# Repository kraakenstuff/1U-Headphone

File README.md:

# 1U-Headphone
1U Eurorack headphone output module based on Befaco Output v3 (https://www.befaco.org/docs/Output/Output_V3_schematic.pdf)

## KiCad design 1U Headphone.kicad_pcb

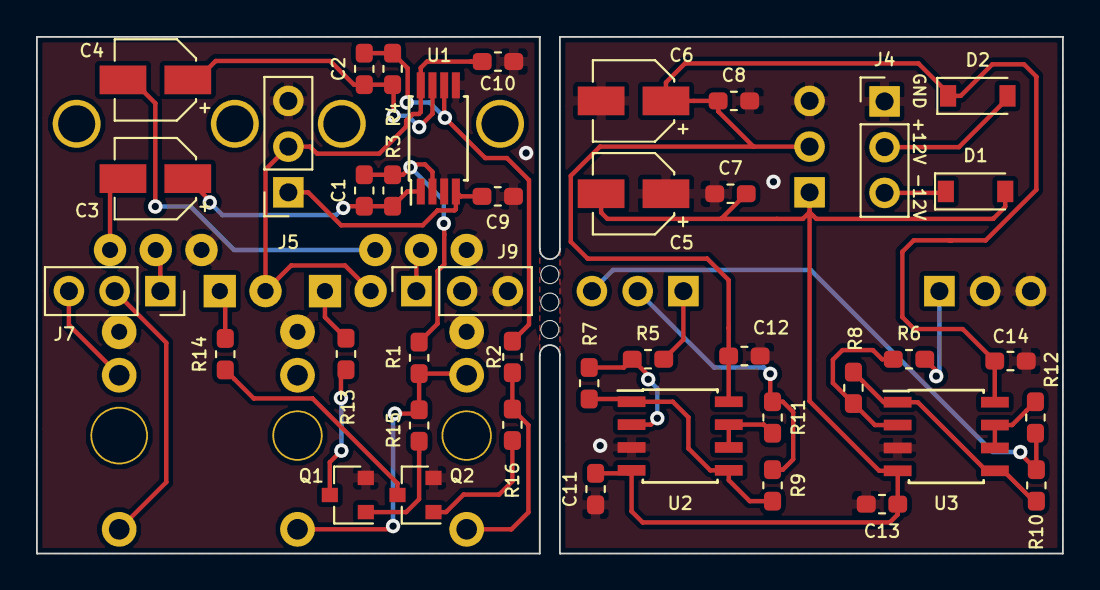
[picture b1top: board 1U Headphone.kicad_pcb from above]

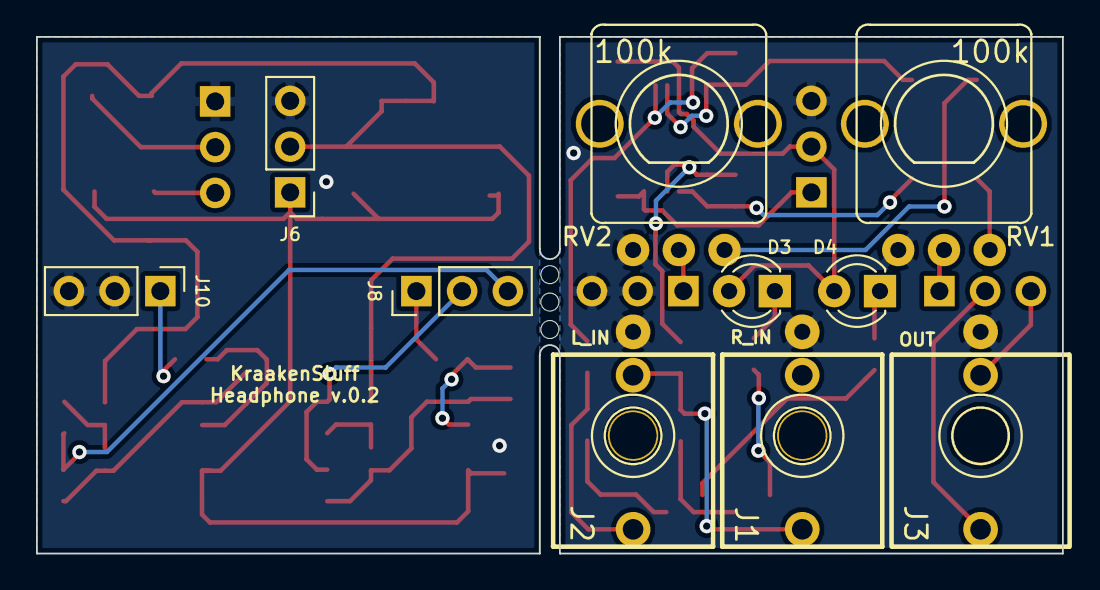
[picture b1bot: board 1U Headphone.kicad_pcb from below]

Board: 2 copper layers, 57.0 x 28.7 mm, 51 parts (10 on the bottom side), 33 nets.

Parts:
C1, C2: 10p; C_0603_1608Metric_Pad1.05x0.95mm_HandSolder
C3, C4, C5, C6: 10uF; CP_Elec_4x5.7
C7, C8, C9, C10, C11, C12, C13, C14: 100n; C_0603_1608Metric_Pad1.05x0.95mm_HandSolder
D1, D2: 1N5817; D_SOD-123
D3, D4: LED; LED_D3.0mm
J1: R_IN; PJ301M-12
J2: L_IN; PJ301M-12
J3: OUT; PJ366ST
J4: PWR; PinHeader_1x03_P2.54mm_Vertical
J5: PWR_C; PinSocket_1x03_P2.54mm_Vertical
J6: PWR_M; PinHeader_1x03_P2.54mm_Vertical
J7: POT_R_C; PinSocket_1x03_P2.54mm_Vertical
J8: POT_R_M; PinHeader_1x03_P2.54mm_Vertical
J9: POT_L_C; PinSocket_1x03_P2.54mm_Vertical
J10: POT_L_M; PinHeader_1x03_P2.54mm_Vertical
Q1, Q2: MMBT3904; SOT-23
R1, R2, R15, R16: 100k; R_0603_1608Metric_Pad1.05x0.95mm_HandSolder
R3, R4: 39k; R_0603_1608Metric_Pad1.05x0.95mm_HandSolder
R5, R6, R7, R8: 10k; R_0603_1608Metric_Pad1.05x0.95mm_HandSolder
R9, R10, R11, R12: 75; R_0603_1608Metric_Pad1.05x0.95mm_HandSolder
R13, R14: 1k; R_0603_1608Metric_Pad1.05x0.95mm_HandSolder
RV1, RV2: 100k; POT-9MM-ALPHA
U1: TL072; TSSOP-8_4.4x3mm_P0.65mm
U2, U3: NE5532; SOIC-8_3.9x4.9mm_P1.27mm

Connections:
+12V: C6.1, C8.1, C10.1, C12.1, C14.1, D2.1, D3.2, D4.2, J5.2, J6.2, U1.8, U2.8, U3.8
-12V: C5.2, C7.2, C9.2, C11.2, C13.2, D1.2, J5.1, J6.1, U1.4, U2.4, U3.4
GND: C5.1, C6.2, C7.1, C8.2, C9.1, C10.2, C11.1, C12.2, C13.1, C14.2, J1.S, J2.S, J3.S, J4.1, J5.3, J6.3, J9.2, J9.3, J10.2, J10.3, Q1.2, Q2.2, RV1.1, RV2.1, U1.3, U1.5, U2.3, U3.3
unnamed: C1.1, C3.1, R3.1, U1.1
unnamed: C1.2, R1.1, R3.2, U1.2
unnamed: C2.1, C4.1, R4.1, U1.7
unnamed: C2.2, R2.1, R4.2, U1.6
unnamed: C3.2, RV1.3
unnamed: C4.2, RV2.3
unnamed: D1.1, J4.3
unnamed: D2.2, J4.2
unnamed: D3.1, R13.2
unnamed: D4.1, R14.2
unnamed: J1.T, J2.TN, R1.2, R15.1
unnamed: J2.T, R2.2, R16.1
unnamed: Q1.1, R15.2
unnamed: Q1.3, R13.1
unnamed: Q2.1, R16.2
unnamed: Q2.3, R14.1
unnamed: R5.1, R7.2, U2.2
unnamed: R6.1, R8.2, U3.2
unnamed: R7.1, R9.2, U2.1, U2.5
unnamed: R8.1, R10.2, U3.1, U3.5
unnamed: R11.2, U2.6, U2.7
unnamed: R12.2, U3.6, U3.7
OUT_L_C: J3.R, J7.3
OUT_L_M: J8.3, R10.1, R12.1
OUT_R_C: J3.T, J7.2
OUT_R_M: J8.2, R9.1, R11.1
POT_L_C: J9.1, RV2.2
POT_L_M: J10.1, R6.2
POT_R_C: J7.1, RV1.2
POT_R_M: J8.1, R5.2

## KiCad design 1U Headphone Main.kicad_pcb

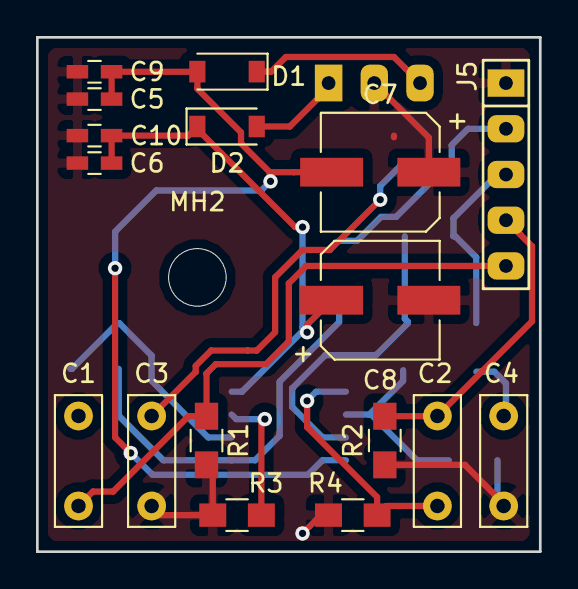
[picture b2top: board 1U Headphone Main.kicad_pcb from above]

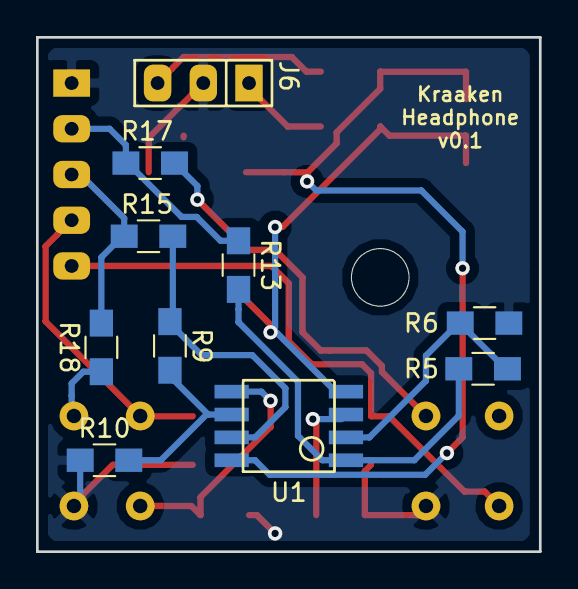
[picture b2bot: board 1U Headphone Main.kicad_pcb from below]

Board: 2 copper layers, 27.9 x 28.6 mm, 28 parts (10 on the bottom side), 17 nets.

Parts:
C1, C2, C3, C4: C; C_Rect_L7.2mm_W2.5mm_P5.00mm_FKS2_FKP2_MKS2_MKP2
C5, C6, C9, C10: C; C_0603_HandSoldering
C7, C8: CP; CP_Elec_6.3x7.7
D1, D2: 1N5817; D_SOD-123
J5: Header_1x05; Header 1x5
J6: Header_1x03; Header 1x3
MH2: MountingHole; MountingHole_3.2mm_M3
R1, R2, R3, R4, R5, R6, R9, R10, R13, R15, R17, R18: R; R_0805_HandSoldering
U1: NJM2068; DMP8

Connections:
+12V: C6.1, C8.1, C10.1, D2.1, U1.4
-12V: C5.2, C7.2, C9.2, D1.2, U1.8
GND: C3.1, C4.1, C5.1, C6.2, C7.1, C8.2, C9.1, C10.2, J5.1, J6.2, R1.2, R2.2, R3.2, R4.2, R6.1, R10.1
L_IN: C1.2, J5.5, R1.1
L_OUT: J5.2, R13.1, R17.2
unnamed: C1.1, R3.1, U1.3
unnamed: C2.1, R4.1, U1.5
unnamed: C3.2, R17.1
unnamed: C4.2, R18.1
unnamed: D1.1, J6.3
unnamed: D2.2, J6.1
unnamed: R5.2, R6.2, U1.2
unnamed: R9.2, R10.2, U1.6
unnamed: R5.1, R13.2, U1.1
unnamed: R9.1, R15.2, U1.7
R_IN: C2.2, J5.4, R2.1
R_OUT: J5.3, R15.1, R18.2

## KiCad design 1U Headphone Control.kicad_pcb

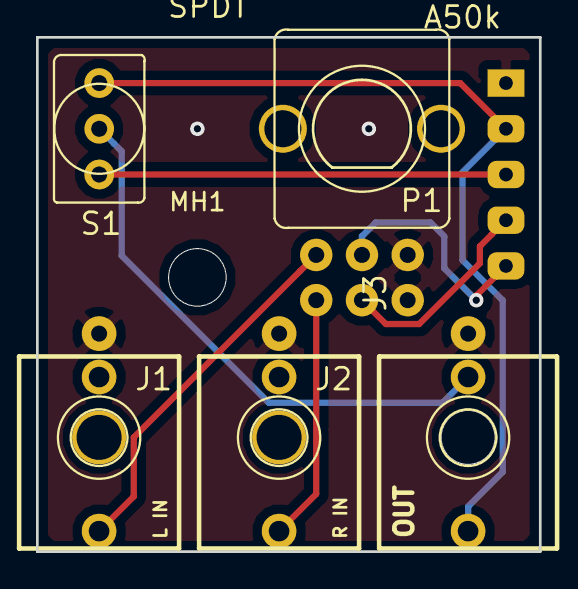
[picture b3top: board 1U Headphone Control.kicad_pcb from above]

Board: 2 copper layers, 27.9 x 28.6 mm, 7 parts (1 on the bottom side), 8 nets.

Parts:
J1: L IN; PJ301M-12
J2: R IN; PJ301M-12
J3: OUT; PJ366ST
J4: Header_1x05; Header 1x5
MH1: MountingHole; MountingHole_3.2mm_M3
P1: A50k; POT-9MM-ALPHA-DUAL
S1: SPDT; SPDT-SUB

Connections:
GND: J1.1, J2.1, J3.1, J4.1, P1.3, P1.6
L_IN: J4.5, P1.2
L_OUT: J3.3, J4.2, S1.3
unnamed: J1.3, P1.1
unnamed: J2.3, P1.4
unnamed: J3.2, S1.2
R_IN: J4.4, P1.5
R_OUT: J4.3, S1.1

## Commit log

2018-11-25 Changed gitignore to the standard one
2019-02-16 Changed everything
2019-03-05 Fixed error in powering op amps
